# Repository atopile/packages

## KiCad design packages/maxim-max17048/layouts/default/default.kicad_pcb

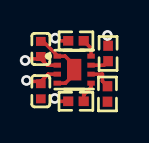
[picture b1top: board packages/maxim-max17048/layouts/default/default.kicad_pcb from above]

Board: 2 copper layers, 7 parts (0 on the bottom side), 7 nets.

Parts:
C1, C2: 1e-06F; C0402
R1, R2, R3, R4: 10000Ω; R0402
U1: TDFN-8_L2.0-W2.0-P0.50-BL-EP1.2

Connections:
QSTRT: R4.1, U1.6
SCL: R2.2, U1.7
SDA: R3.2, U1.8
battery_cap-power-hv: C2.1, U1.2
hv: C1.1, R1.2, R2.1, R3.1, U1.3
lv: C1.2, C2.2, R4.2, U1.1, U1.4, U1.9
nALRT: R1.1, U1.5

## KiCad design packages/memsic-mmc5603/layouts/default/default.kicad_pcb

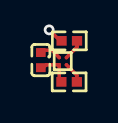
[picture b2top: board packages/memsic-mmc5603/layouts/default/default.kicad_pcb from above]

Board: 2 copper layers, 4 parts (0 on the bottom side), 3 nets.

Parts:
C1: 1F; C0402
R1, R2: 10000Ω; R0402
U1: FLIPCHIP-4_L0.8-W0.8-R2-C2-P0.40-TL

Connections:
SCL: R1.2, U1.A2
SDA: R2.2, U1.B2
hv: R1.1, R2.1, U1.B1

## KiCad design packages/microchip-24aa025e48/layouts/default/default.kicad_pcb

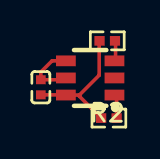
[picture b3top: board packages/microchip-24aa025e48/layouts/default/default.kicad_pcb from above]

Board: 2 copper layers, 4 parts (0 on the bottom side), 4 nets.

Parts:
C1: 0.0000001F; C0402
R1, R2: 4700Ω; R0402
U1: SOT-23-6_L2.9-W1.6-P0.95-LS2.8-BR

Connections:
SCL: R1.1, U1.1
SDA: R2.1, U1.3
hv: C1.1, R1.2, R2.2, U1.6
lv: C1.2, U1.2, U1.4, U1.5
